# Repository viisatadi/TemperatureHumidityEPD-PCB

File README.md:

Temperature/Humidity ePaper Display KiCad Files
===============================================
  
This project is an attempt to port Kevin Kessler's Hackaday project from an STM32L0 MCU to one from Analog Devices. The purpose of this project was to investigate the effort required to switch micros.

From the original repo:
In order to investigate the low power modes and techniques for an STM32L0 class microprocessor, I've build a temperature and humidity display using an STM32L031F6 uC, an SI7021 I2C temperature/humidity sensor, and a Waveshare 1.54 inch black, white, and red ePaperDisplay. Starting with a straight-forward, non-optimized version of the software, this project will investigate and document the various power savings techniques that can be applied to the system, in order to get the power usage of the device down to a level that (hopefully) makes it practical to run off of a CR2032 coin cell. 

Track the progress on [Hackaday.io](https://hackaday.io/project/134018-coin-cell-powered-temperaturehumidity-display)

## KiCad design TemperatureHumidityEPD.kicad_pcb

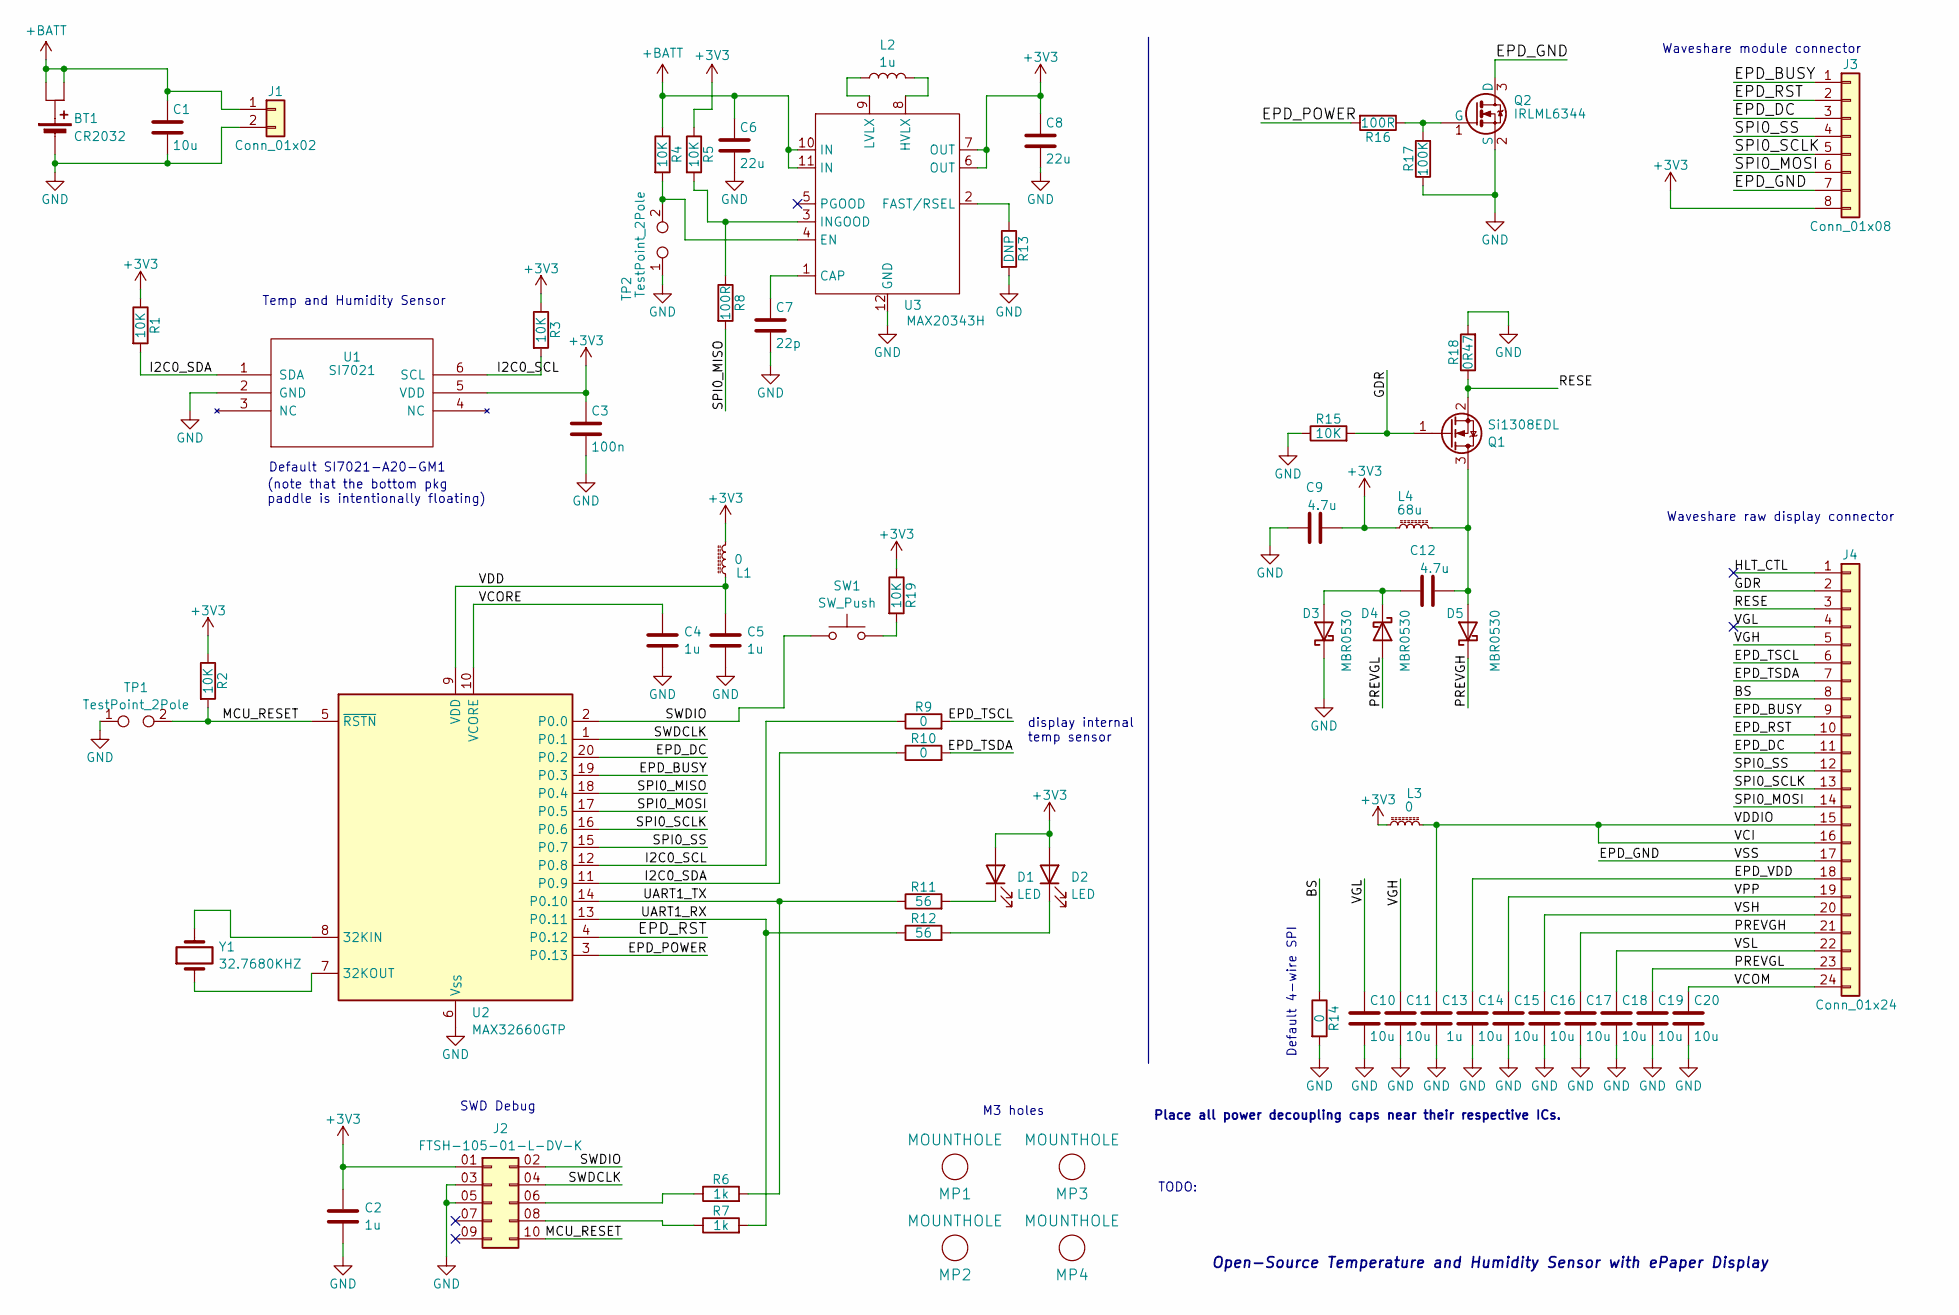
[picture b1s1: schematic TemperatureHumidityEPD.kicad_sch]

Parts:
BT1: CR2032; BatteryHolder_TE_BATT-HLD-000_1x2032; Part Number BAT-HLD-001
C1, C10, C11, C14, C15, C16, C17, C18, C19, C20: 10u; C_0603_1608Metric_Pad1.08x0.95mm_HandSolder; Part Number GRM188D71A106KA73J
C2, C4, C5, C13: 1u; C_0603_1608Metric_Pad1.08x0.95mm_HandSolder; Part Number C1608X7R1A105K080AC
C3: 100n; C_0603_1608Metric_Pad1.08x0.95mm_HandSolder; Part Number C0603C104K3RACTU
C6, C8: 22u; C_1206_3216Metric_Pad1.33x1.80mm_HandSolder; Part Number GRM31CR70J226KE19L
C7: 22p; C_0603_1608Metric_Pad1.08x0.95mm_HandSolder; Part Number CC0603JRNPO9BN220
C9, C12: 4.7u; C_0805_2012Metric_Pad1.18x1.45mm_HandSolder; Part Number GRM21BC71E475KE11L
D1, D2: LED; LED_0805_2012Metric_Pad1.15x1.40mm_HandSolder; Part Number IN-S85AT5UW
D3, D4, D5: MBR0530; D_SOD-123; Part Number MBR0530T1G
J1: Conn_01x02; Pin_Header_Straight_1x02_Pitch2.54mm
J2: FTSH-105-01-L-DV-K; SAMTEC_FTSH-105-01-L-DV-K; Part Number FTSH-105-01-L-DV-K
J3: Conn_01x08; JST_PH_S8B-PH-SM4-TB_1x08-1MP_P2.00mm_Horizontal
J4: Conn_01x24; TE_2-1734839-4_1x24-1MP_P0.5mm_Horizontal_reversednumber; Part Number 2-1734839-4
L1, L3: 0; R_0603_1608Metric_Pad0.98x0.95mm_HandSolder; Part Number RCS06030000Z0EC
L2: 1u; L_0805_2016Metric; Part Number MLP2016S1R0MT0S1
L4: 68u; L_3x3_H3; Part Number SDR0302-680KL
MP1, MP2, MP3, MP4: MOUNTHOLE; TH-M3
Q1: Si1308EDL; SOT-323_SC-70; Part Number Si1308EDL-T1-GE3
Q2: IRLML6344; SOT-23-3; Part Number IRLML6344TRPBF
R1, R2, R3, R4, R5, R15, R19: 10K; R_0603_1608Metric_Pad0.98x0.95mm_HandSolder; Part Number RT0603FRE0710KL
R6, R7: 1k; R_0603_1608Metric_Pad0.98x0.95mm_HandSolder; Part Number RT0603FRE131KL
R8, R16: 100R; R_0603_1608Metric_Pad0.98x0.95mm_HandSolder; Part Number RT0603FRE07100RL
R9, R10, R14: 0; R_0603_1608Metric_Pad0.98x0.95mm_HandSolder; Part Number RCS06030000Z0EC
R11, R12: 56; R_0603_1608Metric_Pad0.98x0.95mm_HandSolder; Part Number RC0603FR-0756RL
R13: DNP; R_0603_1608Metric_Pad0.98x0.95mm_HandSolder; Part Number RCS06030000Z0EC
R17: 100K; R_0603_1608Metric_Pad0.98x0.95mm_HandSolder; Part Number RT0603FRE07100KL
R18: 0R47; R_0805_2012Metric_Pad1.20x1.40mm_HandSolder; Part Number 2-2176054-4
SW1: SW_Push; Panasonic_EVQPUJ_EVQPUA; Part Number EVQ-P7A01P
TP1, TP2: TestPoint_2Pole; TestPoint_Padx2_D2.0mm
U1: SI7021; Part Number SI7021-A20-GM1
U2: MAX32660GTP; TQFN-20-1EP_4x4mm_P0.5mm_EP2.7x2.7mm; Part Number MAX32660GTP
U3: MAX20343H; Part Number MAX20343HEFC+
Y1: 32.7680KHZ; Crystal_SMD_MicroCrystal_CM9V-T1A-2Pin_1.6x1.0mm_HandSolder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; Part Number CM1610H32768DZB

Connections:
+3V3: C2.1, C3.1, C8.1, C9.2, D1.2 (A), D2.2 (A), J2.01 (Pin_1), J3.8, L1.2, L3.1, L4.1, R1.1, R2.1, R3.1, R5.1, R19.1, U1.5 (VDD), U3.6 (OUT), U3.7 (OUT)
+BATT: BT1.1 (+), BT1.2 (+), C1.1, C6.1, J1.1, R4.1, U3.10 (IN), U3.11 (IN)
/BS: J4.8, R14.1
/EPD_BUSY: J3.1, J4.9, U2.19 (P0.3)
/EPD_DC: J3.3, J4.11, U2.20 (P0.2)
/EPD_GND: J3.7, J4.17, Q2.3 (D)
/EPD_POWER: R16.2, U2.3 (P0.13)
/EPD_RST: J3.2, J4.10, U2.4 (P0.12)
/EPD_TSCL: J4.6, R9.2
/EPD_TSDA: J4.7, R10.2
/EPD_VDD: C14.1, J4.18
/GDR: J4.2, Q1.1 (G), R15.2
/HLT_CTL: J4.1
/I2C0_SCL: R3.2, R9.1, U1.6 (SCL), U2.12 (P0.8)
/I2C0_SDA: R1.2, R10.1, U1.1 (SDA), U2.11 (P0.9)
/MCU_RESET: J2.10, R2.2, TP1.2, U2.5 (~RSTN)
/PREVGH: C17.1, D5.1 (K), J4.21
/PREVGL: C19.1, D4.2 (A), J4.23
/RESE: J4.3, Q1.2 (S), R18.1
/SPI0_MISO: R8.2, U2.18 (P0.4)
/SPI0_MOSI: J3.6, J4.14, U2.17 (P0.5)
/SPI0_SCLK: J3.5, J4.13, U2.16 (P0.6)
/SPI0_SS: J3.4, J4.12, U2.15 (P0.7)
/SWDCLK: J2.04 (Pin_4), U2.1 (P0.1)
/SWDIO: J2.02 (Pin_2), SW1.1, U2.2 (P0.0)
/UART1_RX: R7.2, R12.1, U2.13 (P0.11)
/UART1_TX: R6.2, R11.1, U2.14 (P0.10)
/VCI: C13.1, J4.15, J4.16, L3.2
/VCOM: C20.1, J4.24
/VCORE: C4.1, U2.10 (VCORE)
/VDD: C5.1, L1.1, U2.9 (VDD)
/VGH: C11.1, J4.5
/VGL: C10.1, J4.4
/VPP: C15.1, J4.19
/VSH: C16.1, J4.20
/VSL: C18.1, J4.22
GND: BT1.3 (-), C1.2, C2.2, C3.2, C4.2, C5.2, C6.2, C7.2, C8.2, C9.1, C10.2, C11.2, C13.2, C14.2, C15.2, C16.2, C17.2, C18.2, C19.2, C20.2, D3.1 (K), J1.2, J2.03 (Pin_3), J2.05 (Pin_5), Q2.2 (S), R13.2, R14.2, R15.1, R17.1, R18.2, TP1.1, TP2.1, U1.2 (GND), U2.6 (V_{SS}), U2.21 (V_{SS}), U3.12 (GND)
unnamed: D1.1 (K), R11.2
unnamed: D2.1 (K), R12.2
unnamed: C12.1, D3.2 (A), D4.1 (K)
unnamed: C12.2, D5.2 (A), L4.2, Q1.3 (D)
unnamed: J2.06 (Pin_6), R6.1
unnamed: J2.08 (Pin_8), R7.1
unnamed: Q2.1 (G), R16.1, R17.2
unnamed: R19.2, SW1.2
unnamed: U2.8 (32KIN), Y1.2
unnamed: U2.7 (32KOUT), Y1.1
unnamed: C7.1, U3.1 (CAP)
unnamed: R4.2, TP2.2, U3.4 (EN)
unnamed: R13.1, U3.2 (FAST/RSEL)
unnamed: L2.2, U3.8 (HVLX)
unnamed: R5.2, R8.1, U3.3 (INGOOD)
unnamed: L2.1, U3.9 (LVLX)

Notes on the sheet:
Default 4-wire SPI
(note that the bottom pkg paddle is intentionally floating)
Open-Source Temperature and Humidity Sensor with ePaper Display
Place all power decoupling caps near their respective ICs.
display internal temp sensor
Temp and Humidity Sensor
Waveshare module connector
TODO:
Waveshare raw display connector
M3 holes
SWD Debug
Default SI7021-A20-GM1

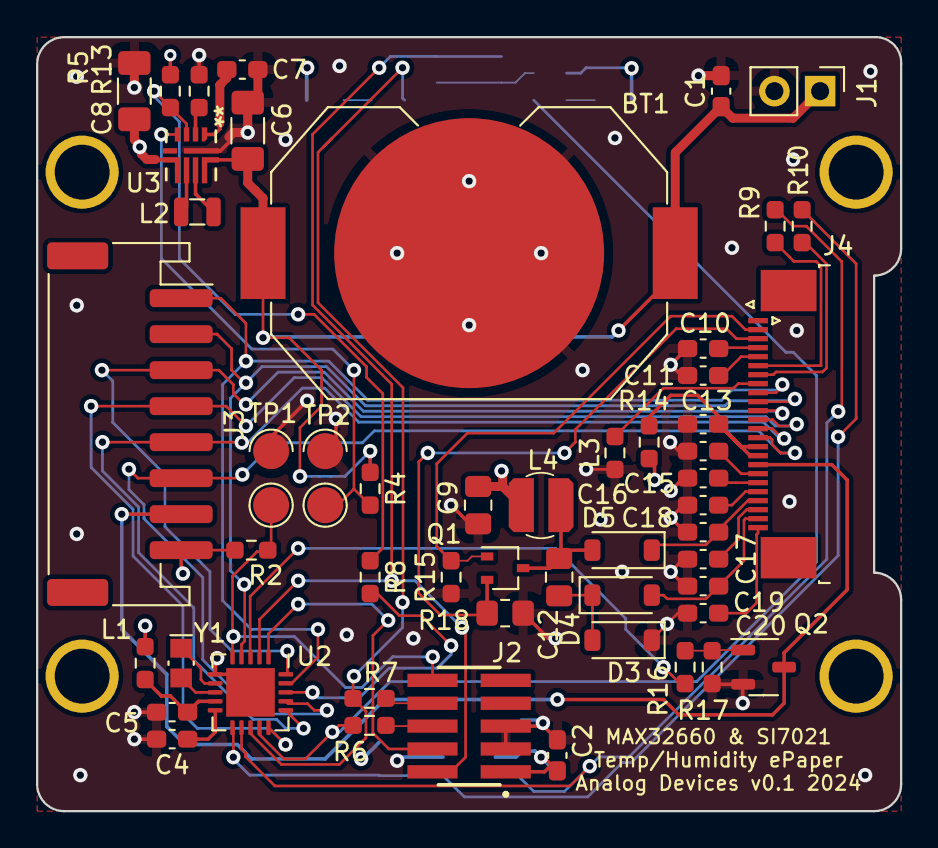
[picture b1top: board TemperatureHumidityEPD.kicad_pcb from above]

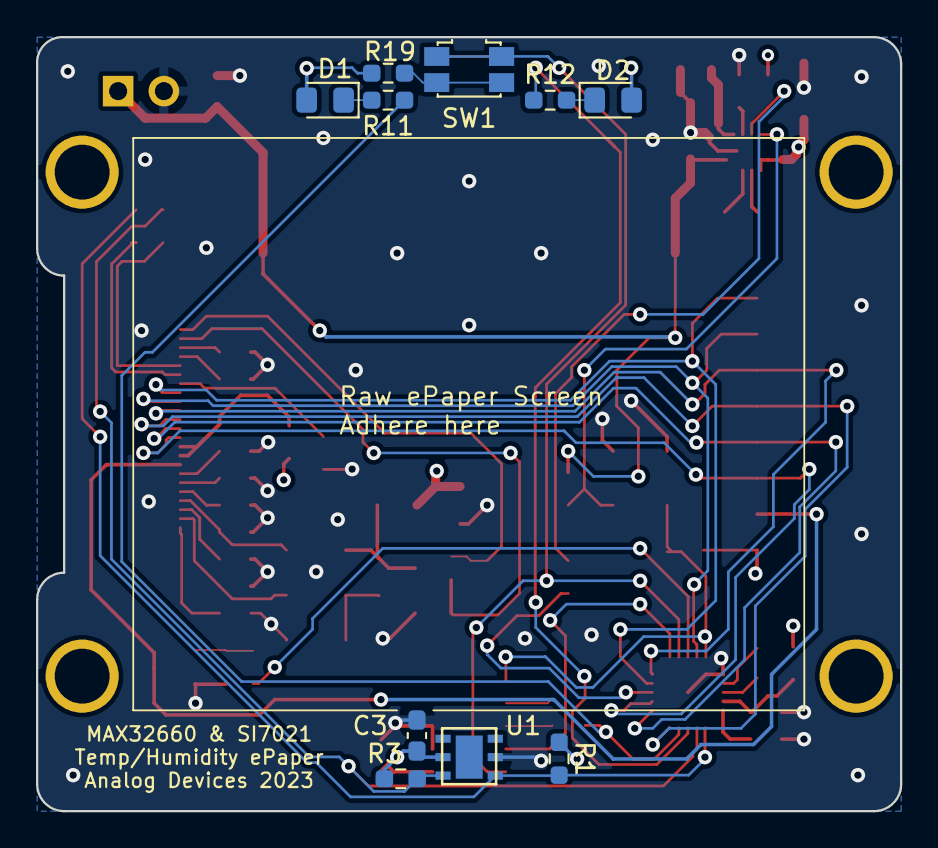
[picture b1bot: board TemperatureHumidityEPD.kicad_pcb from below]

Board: 4 copper layers, 48.0 x 43.0 mm, 66 parts (10 on the bottom side), 52 nets.

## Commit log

2023-11-29 Edits of the schematic, porting the design to MAX32660.
    Full part number information added in the schematic.
    Footprints linked. However, two parts need new footprints: 68uH inductor and the SWD debug connector.
    Related to this TODO: final check of the FPC connector.
    Group review of the schematic is now in progress.
2023-11-29 Added buck-boost for constant 3.3Vout.
    Fixes for ePaper display power.
    Double-check part availability.
    Final footprint reference changes in schematic.
2023-12-01 Completely finished layout. Various small schematic tweaks along the way of layout.
2023-12-01 Fix schematic date, update PDF
2023-12-01 Fix backside silkscreen. Added outline of raw display. Regenerated fab files.
2023-12-01 deleting unused artifact archive file from original design
2023-12-01 Fix Part Number for 1k resistor
2024-03-04 Reversed D1 polarity in schematic and PCB. Moved INGOOD pull-up to 3V3 from input net +BATT. Update version and date.
